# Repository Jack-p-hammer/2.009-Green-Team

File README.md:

Control logic and arduino code for MIT 2025 2.009 Green Team's project.

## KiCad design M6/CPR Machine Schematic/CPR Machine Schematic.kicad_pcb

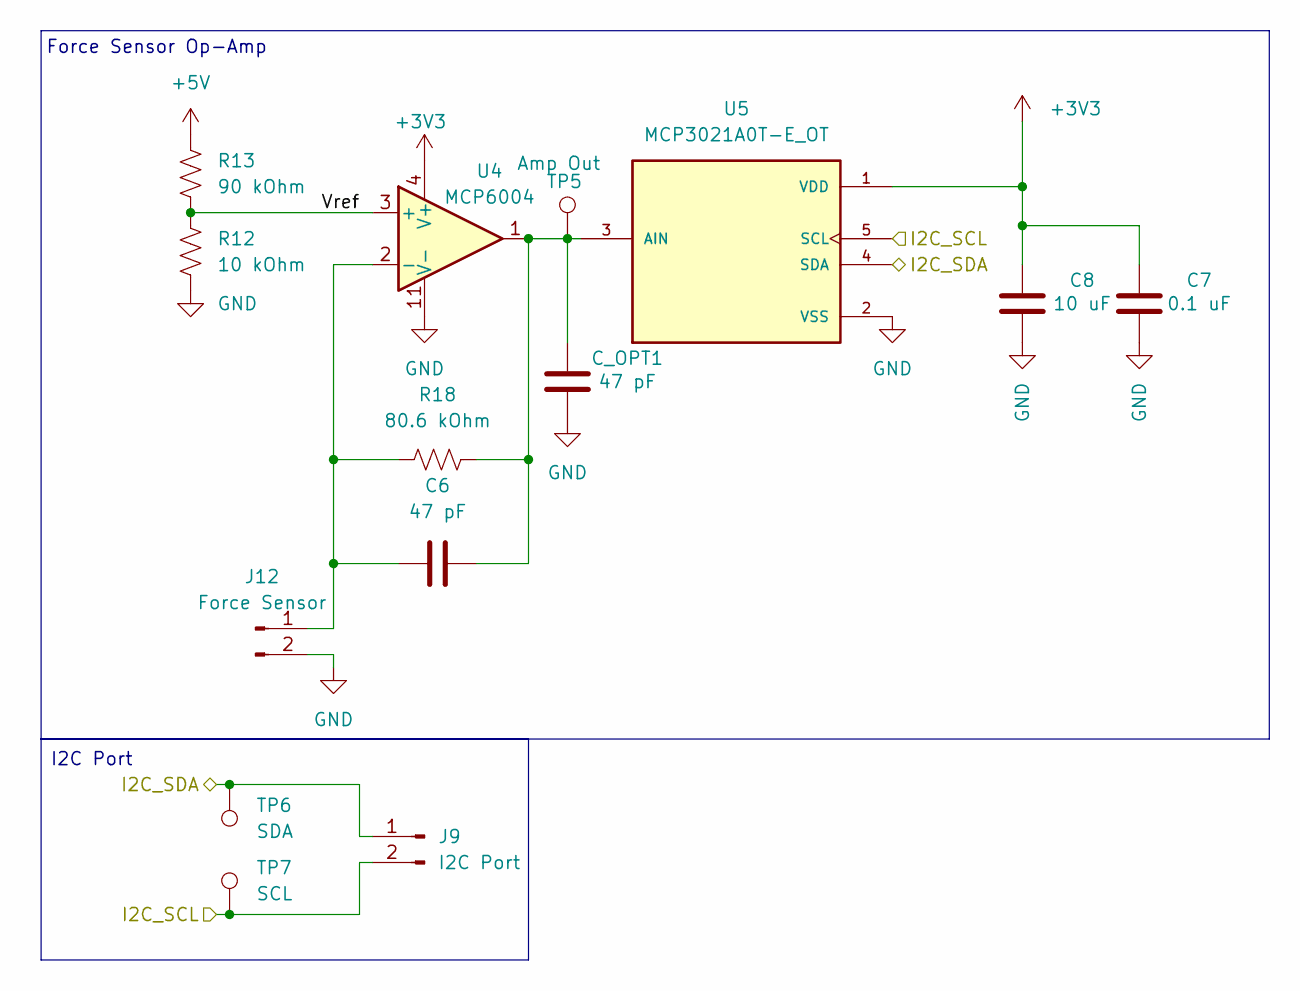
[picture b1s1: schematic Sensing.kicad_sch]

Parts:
C6: 47 pF; C_1206_3216Metric_Pad1.33x1.80mm_HandSolder; digikey 1292-1206N470J102CT-ND
C7: 0.1 uF; C_1206_3216Metric_Pad1.33x1.80mm_HandSolder
C8: 10 uF; C_1206_3216Metric_Pad1.33x1.80mm_HandSolder
C_OPT1: 47 pF; C_1206_3216Metric_Pad1.33x1.80mm_HandSolder
J9: I2C Port; PinHeader_1x02_P2.54mm_Vertical
J12: Force Sensor; TerminalBlock_MaiXu_MX126-5.0-02P_1x02_P5.00mm; digikey 277-1667-ND
R12: 10 kOhm; R_1206_3216Metric_Pad1.30x1.75mm_HandSolder
R13: 90 kOhm; R_1206_3216Metric_Pad1.30x1.75mm_HandSolder; digikey 13-RT1206DRE0790KLCT-ND
R18: 80.6 kOhm; R_1206_3216Metric_Pad1.30x1.75mm_HandSolder; digikey 311-80.6FRCT-ND
TP5: Amp Out; TestPoint_Pad_D1.5mm
TP6: SDA; TestPoint_Pad_D1.5mm
TP7: SCL; TestPoint_Pad_D1.5mm
U4: MCP6004; SOIC14_SL_MCH; digikey MCP6004T-I/SLCT-ND
U5: MCP3021A0T-E_OT; IC_MCP3021A0T-E_OT; PARTREV D; DigiKey_Part_Number MCP3021A0T-E/OTCT-ND

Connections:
+3V3: C7.2, C8.2, U4.4 (V+), U5.1 (VDD)
+5V: R13.1; also elsewhere on the board
/Raspi/I2C_SCL: J9.2, TP7.1, U5.5 (SCL); also elsewhere on the board
/Raspi/I2C_SDA: J9.1, TP6.1, U5.4 (SDA); also elsewhere on the board
/Sensing/Vref: R12.1, R13.2, U4.3 (+)
GND: C7.1, C8.1, C_OPT1.1, J12.2, R12.2, U4.11 (V-), U5.2 (VSS); also elsewhere on the board
unnamed: C6.1, J12.1, R18.2, U4.2 (-)
unnamed: C6.2, C_OPT1.2, R18.1, TP5.1, U4.1, U5.3 (AIN)

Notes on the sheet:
I2C Port
Force Sensor Op-Amp

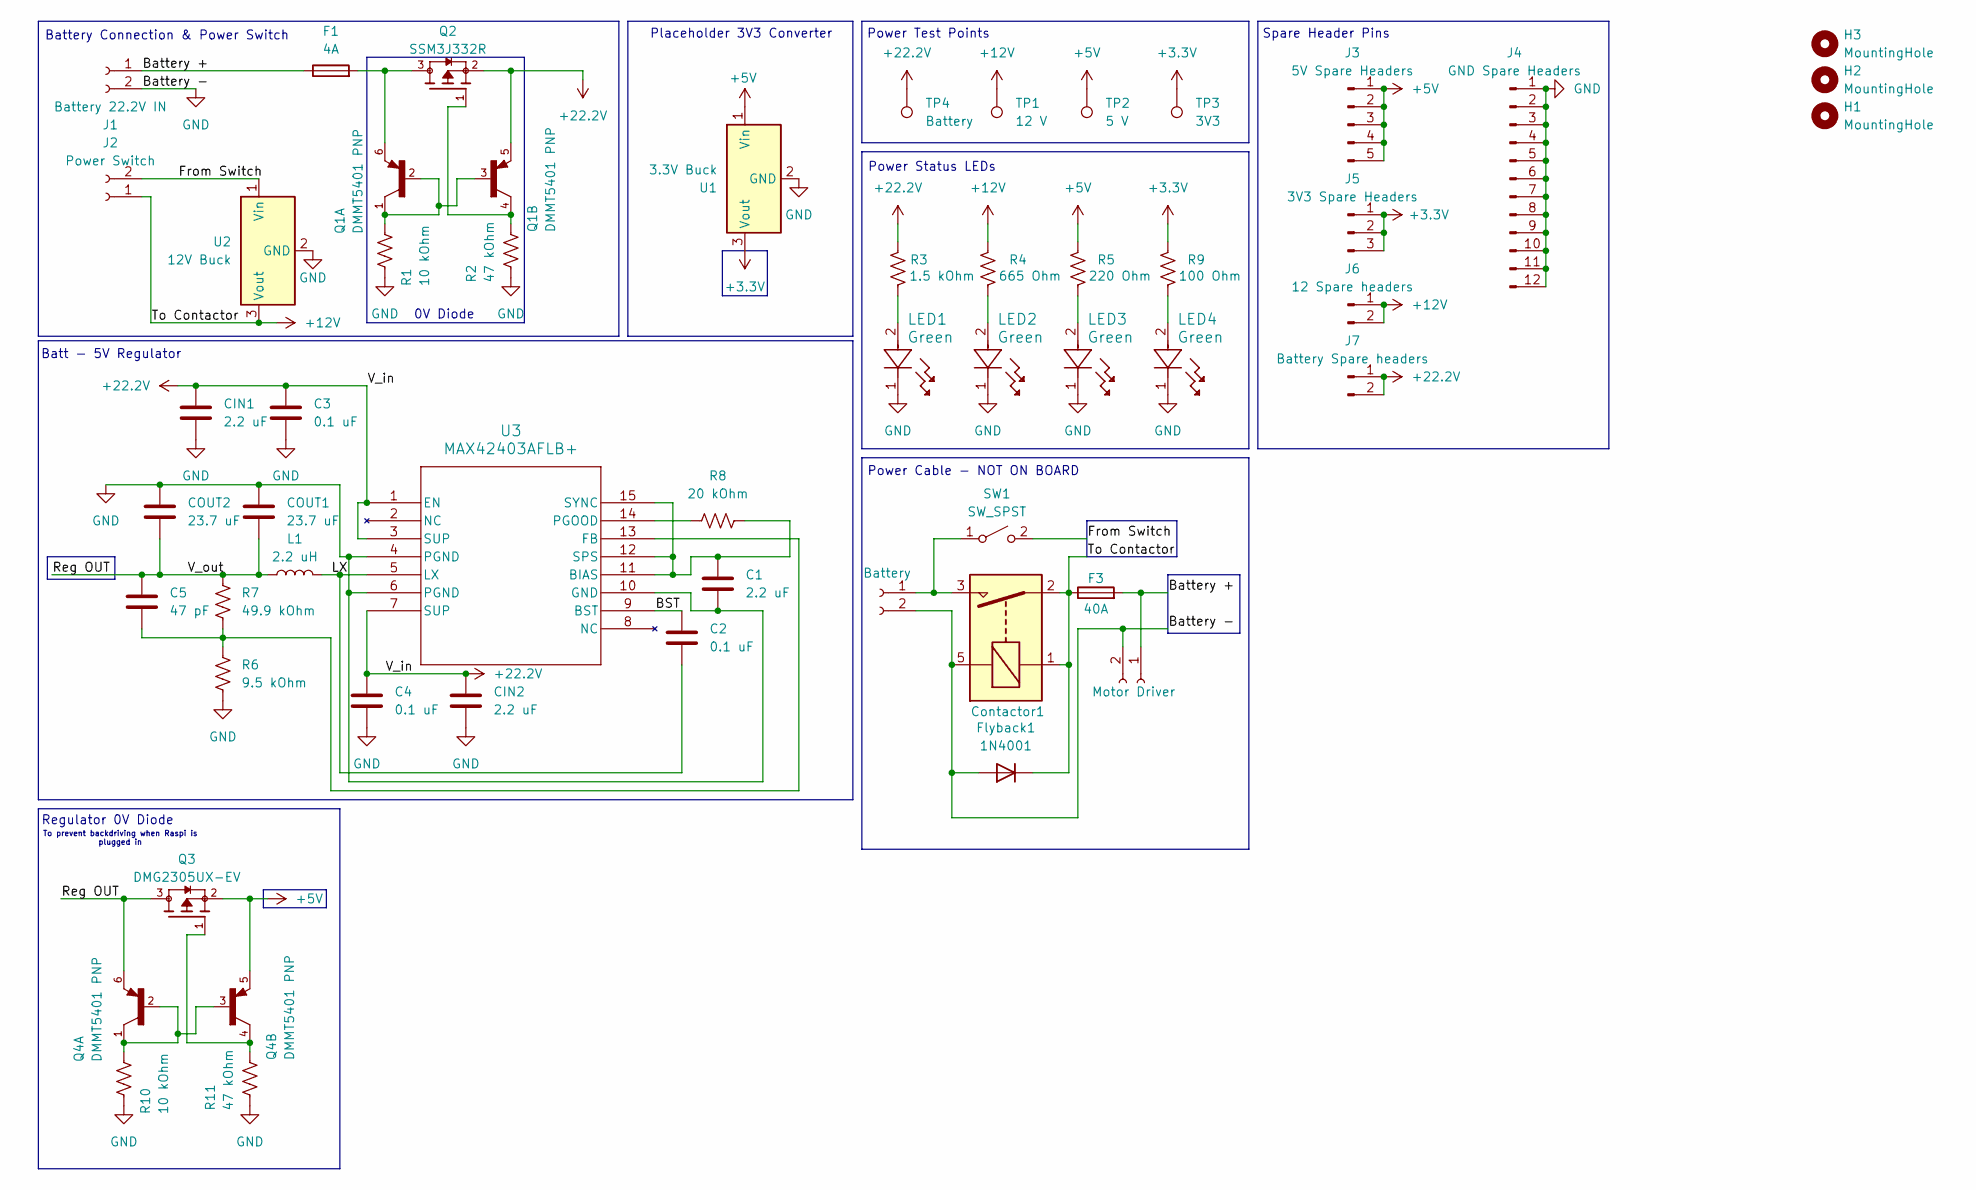
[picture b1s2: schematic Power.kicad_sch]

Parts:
C1: 2.2 uF; C_1206_3216Metric_Pad1.33x1.80mm_HandSolder; digikey 490-17674-1-ND
C2, C3, C4: 0.1 uF; C_1206_3216Metric_Pad1.33x1.80mm_HandSolder; digikey 490-GRM3195C1H104JA05DCT-ND
C5: 47 pF; C_1206_3216Metric_Pad1.33x1.80mm_HandSolder; digikey 1292-1206N470J102CT-ND
CIN1, CIN2: 2.2 uF; C_1206_3216Metric_Pad1.33x1.80mm_HandSolder; digikey 490-17674-1-ND
COUT1, COUT2: 23.7 uF; C_1210_3225Metric_Pad1.33x2.70mm_HandSolder; digikey 490-5312-1-ND
Contactor1: G5Q-1A; Relay_SPST_Omron-G5Q-1A
F1: 4A; Fuse_1206_3216Metric_Pad1.42x1.75mm_HandSolder; digikey 5923-0685T4000-01CT-ND
F3: 40A; Fuse_1206_3216Metric_Pad1.42x1.75mm_HandSolder; digikey 5923-0685T4000-01CT-ND
Flyback1: 1N4001; D_DO-41_SOD81_P10.16mm_Horizontal
H1, H2, H3: MountingHole; MountingHole_2.7mm_M2.5_Pad
J1: Battery 22.2V IN; AMASS_XT30PW-M_1x02_P2.50mm_Horizontal
J2: Power Switch; AMASS_XT30PW-M_1x02_P2.50mm_Horizontal
J3: 5V Spare Headers; PinHeader_1x05_P2.54mm_Vertical
J4: GND Spare Headers; PinHeader_1x12_P2.54mm_Vertical
J5: 3V3 Spare Headers; PinHeader_1x03_P2.54mm_Vertical
J6: 12 Spare headers; PinHeader_1x02_P2.54mm_Vertical
J7: Battery Spare headers; PinHeader_1x02_P2.54mm_Vertical
J16: Motor Driver
J_EXT1: Battery
L1: 2.2 uH; IND_1217AS-H-2R2N=P3; digikey 490-10787-1-ND
LED1, LED2, LED3, LED4: Green; LED_LTST-C170GKT_LTO; digikey 160-1179-1-ND
Q1, Q4: DMMT5401 PNP; SOT95P285X140-6N; PARTREV 8; digikey DMMT5401-FDICT-ND
Q2: SSM3J332R; SOT-23_Handsoldering; digikey SSM3J332RLFCT-ND
Q3: DMG2305UX-EV; SOT-23_Handsoldering; digikey 5272-DMG2305UX-EVCT-ND
R1, R10: 10 kOhm; R_1206_3216Metric_Pad1.30x1.75mm_HandSolder
R2, R11: 47 kOhm; R_1206_3216Metric_Pad1.30x1.75mm_HandSolder; digikey A129830CT-ND
R3: 1.5 kOhm; R_1206_3216Metric_Pad1.30x1.75mm_HandSolder; digikey RMCF1206JG1K50CT-ND
R4: 665 Ohm; R_1206_3216Metric_Pad1.30x1.75mm_HandSolder; digikey 311-665FRCT-ND
R5: 220 Ohm; R_1206_3216Metric_Pad1.30x1.75mm_HandSolder
R6: 9.5 kOhm; R_1206_3216Metric_Pad1.30x1.75mm_HandSolder; digikey 311-9.53KFRCT-ND
R7: 49.9 kOhm; R_1206_3216Metric_Pad1.30x1.75mm_HandSolder; digikey 311-49.9KFRCT-ND
R8: 20 kOhm; R_1206_3216Metric_Pad1.30x1.75mm_HandSolder; digikey RMCF1206FT20K0CT-ND
R9: 100 Ohm; R_1206_3216Metric_Pad1.30x1.75mm_HandSolder
SW1: SW_SPST
TP1: 12 V; TestPoint_THTPad_D4.0mm_Drill2.0mm
TP2: 5 V; TestPoint_THTPad_D4.0mm_Drill2.0mm
TP3: 3V3; TestPoint_THTPad_D4.0mm_Drill2.0mm
TP4: Battery; TestPoint_THTPad_4.0x4.0mm_Drill2.0mm
U1: 3.3V Buck; Converter_DCDC_TRACO_TSR-1_THT; digikey 1951-2742-ND
U2: 12V Buck; Converter_DCDC_TRACO_TSR-1_THT; digikey 1951-2739-ND
U3: MAX42403AFLB+; 21-100701_90-100241_ADI; digikey 505-MAX42403AFLB+-ND

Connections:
+3.3V: J5.1, J5.2, J5.3, R9.2, TP3.1, U1.3 (Vout); also elsewhere on the board
+5V: J3.1, J3.2, J3.3, J3.4, J3.5, Q3.2, Q4.5, R5.2, TP2.1, U1.1 (Vin); also elsewhere on the board
+12V: Contactor1.1, Contactor1.2, F3.1, Flyback1.1 (K), J2.1, J6.1, J6.2, R4.2, TP1.1, U2.3 (Vout)
+22.2V: C3.2, C4.2, CIN1.2, CIN2.2, J7.1, J7.2, Q1.5, Q2.2, R3.2, TP4.1, U3.1 (EN), U3.3 (SUP), U3.7 (SUP)
/Power/BST: C2.2, U3.9 (BST)
/Power/Battery +: F1.1, F3.2, J1.1, J16.1
/Power/From Switch: J2.2, SW1.2 (B), U2.1 (Vin)
/Power/LX: C2.1, L1.2, U3.5 (LX)
/Power/Reg OUT: C5.2, COUT1.1, COUT2.1, L1.1, Q3.3, Q4.6, R7.1
GND: C1.1, C3.1, C4.1, CIN1.1, CIN2.1, COUT1.2, COUT2.2, Contactor1.5, Flyback1.2 (A), J1.2, J4.1, J4.2, J4.3, J4.4, J4.5, J4.6, J4.7, J4.8, J4.9, J4.10, J4.11, J4.12, J16.2, J_EXT1.2, LED1.1, LED2.1, LED3.1, LED4.1, R1.2, R2.2, R6.2, R10.2, R11.2, U1.2 (GND), U2.2 (GND), U3.4 (PGND), U3.6 (PGND), U3.10 (GND); also elsewhere on the board
unnamed: Contactor1.3, J_EXT1.1, SW1.1 (A)
unnamed: F1.2, Q1.6, Q2.3
unnamed: LED1.2, R3.1
unnamed: LED2.2, R4.1
unnamed: LED3.2, R5.1
unnamed: LED4.2, R9.1
unnamed: Q1.4, Q2.1, R2.1
unnamed: Q1.1, Q1.2, Q1.3, R1.1
unnamed: Q4.1, Q4.2, Q4.3, R10.1
unnamed: Q3.1, Q4.4, R11.1
unnamed: C1.2, R8.2, U3.11 (BIAS), U3.12 (SPS), U3.15 (SYNC)
unnamed: C5.1, R6.1, R7.2, U3.13 (FB)
unnamed: R8.1, U3.14 (PGOOD)

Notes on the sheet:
To prevent backdriving when Raspi is plugged in
Battery Connection & Power Switch
Regulator 0V Diode
Batt - 5V Regulator
Power Cable - NOT ON BOARD
Spare Header Pins
Power Status LEDs
Placeholder 3V3 Converter
Power Test Points
0V Diode

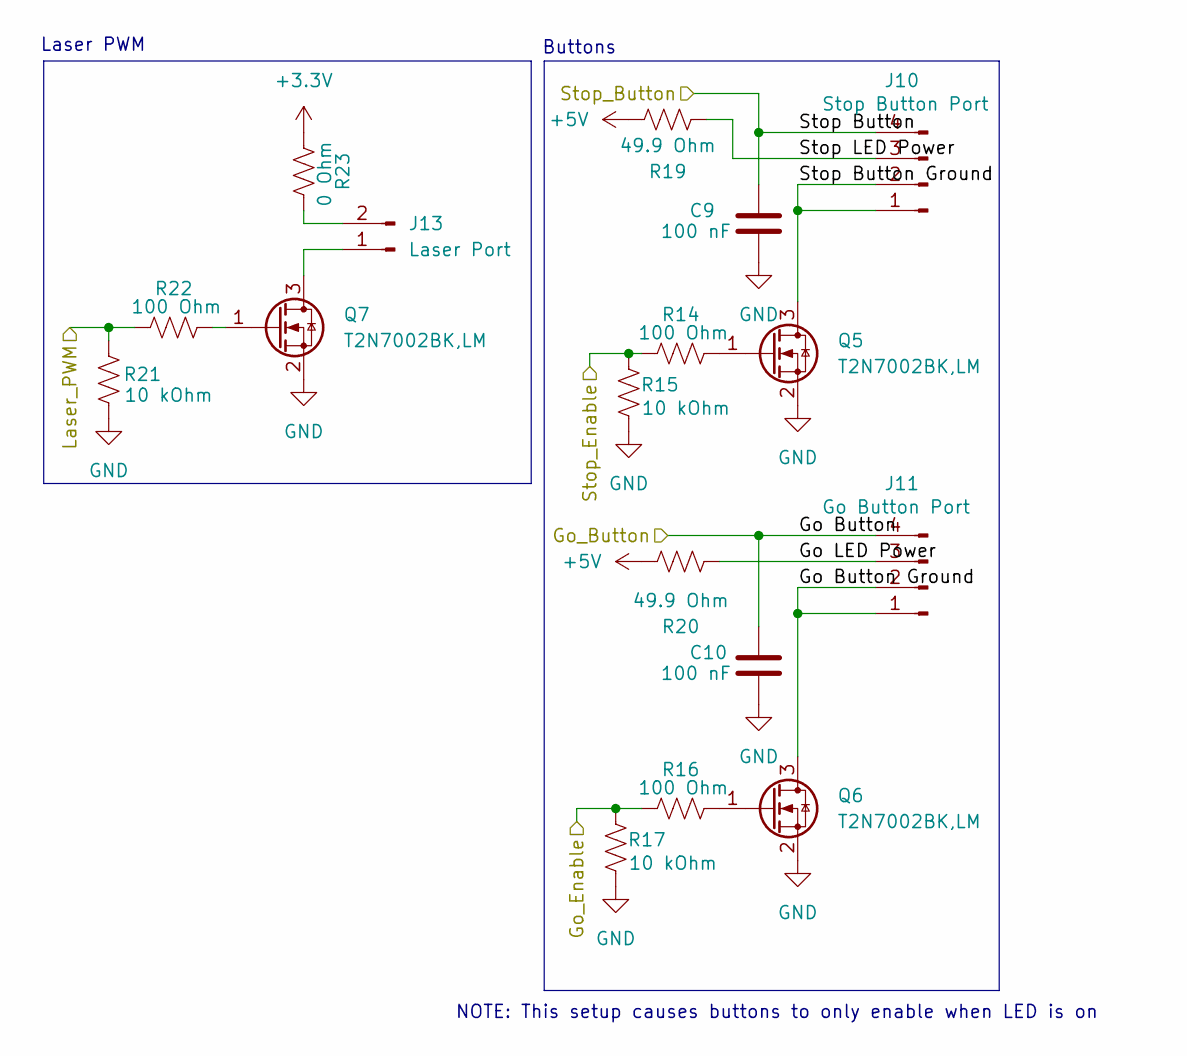
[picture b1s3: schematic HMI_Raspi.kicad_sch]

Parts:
C9, C10: 100 nF; C_1206_3216Metric_Pad1.33x1.80mm_HandSolder
J10: Stop Button Port; PinHeader_1x04_P2.54mm_Vertical
J11: Go Button Port; PinHeader_1x04_P2.54mm_Vertical
J13: Laser Port; TerminalBlock_MaiXu_MX126-5.0-02P_1x02_P5.00mm; digikey 277-1667-ND
Q5, Q6, Q7: T2N7002BK,LM; SOT-23_Handsoldering; digikey T2N7002BKLMCT-ND
R14, R16, R22: 100 Ohm; R_1206_3216Metric_Pad1.30x1.75mm_HandSolder
R15, R17, R21: 10 kOhm; R_1206_3216Metric_Pad1.30x1.75mm_HandSolder
R19, R20: 49.9 Ohm; R_1206_3216Metric_Pad1.30x1.75mm_HandSolder; digikey 311-49.9FRCT-ND
R23: 0 Ohm; R_1206_3216Metric_Pad1.30x1.75mm_HandSolder; digikey RMCF1206ZT0R00CT-ND

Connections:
+3.3V: R23.1; also elsewhere on the board
+5V: R19.2, R20.2; also elsewhere on the board
/HMI_Raspi/Go Button: C10.2, J11.4; also elsewhere on the board
/HMI_Raspi/Go Button Ground: J11.1, J11.2, Q6.3 (D)
/HMI_Raspi/Go LED Power: J11.3, R20.1
/HMI_Raspi/Go_Enable: R16.1, R17.1; also elsewhere on the board
/HMI_Raspi/Laser_PWM: R21.1, R22.1; also elsewhere on the board
/HMI_Raspi/Stop Button: C9.2, J10.4; also elsewhere on the board
/HMI_Raspi/Stop Button Ground: J10.1, J10.2, Q5.3 (D)
/HMI_Raspi/Stop LED Power: J10.3, R19.1
/HMI_Raspi/Stop_Enable: R14.1, R15.1; also elsewhere on the board
GND: C9.1, C10.1, Q5.2 (S), Q6.2 (S), Q7.2 (S), R15.2, R17.2, R21.2; also elsewhere on the board
unnamed: J13.1, Q7.3 (D)
unnamed: J13.2, R23.2
unnamed: Q5.1 (G), R14.2
unnamed: Q7.1 (G), R22.2
unnamed: Q6.1 (G), R16.2

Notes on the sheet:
Buttons
Laser PWM
NOTE: This setup causes buttons to only enable when LED is on

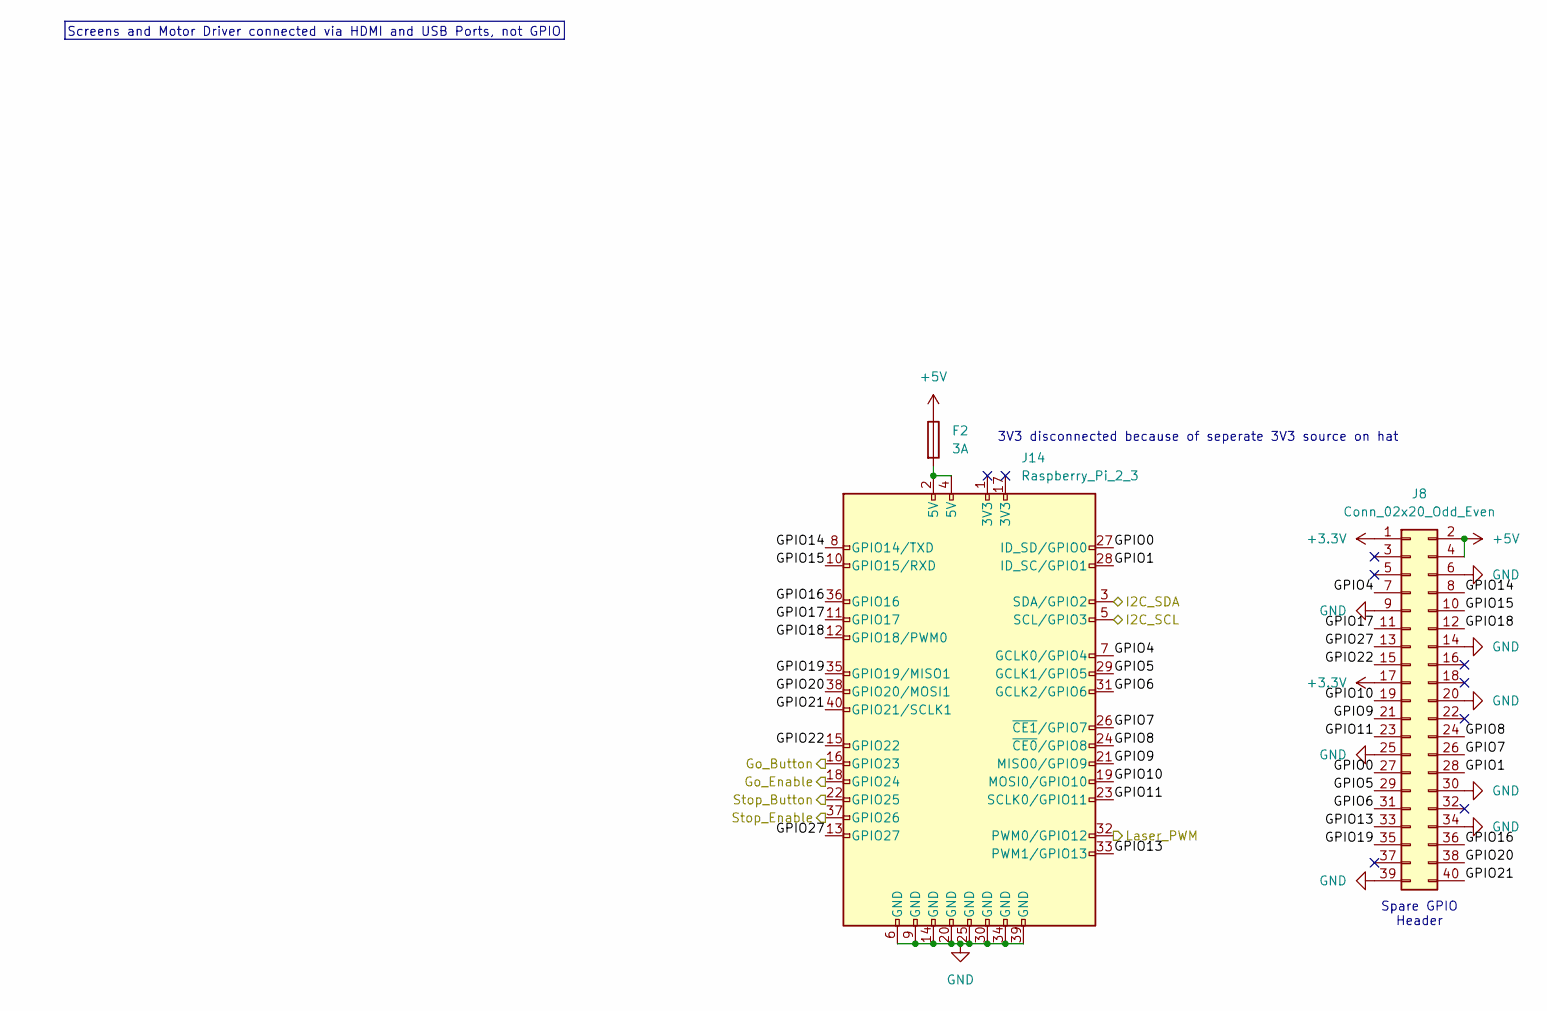
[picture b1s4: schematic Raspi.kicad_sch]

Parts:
F2: 3A; Fuse_1206_3216Metric_Pad1.42x1.75mm_HandSolder; digikey 5923-C1F3CT-ND
J8: Conn_02x20_Odd_Even; PinHeader_2x20_P2.54mm_Vertical
J14: Raspberry_Pi_2_3; PinSocket_2x20_P2.54mm_Vertical

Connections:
+3.3V: J8.1, J8.17; also elsewhere on the board
+5V: F2.1, J8.2, J8.4; also elsewhere on the board
/HMI_Raspi/Go Button: J14.16 (GPIO23); also elsewhere on the board
/HMI_Raspi/Go_Enable: J14.18 (GPIO24); also elsewhere on the board
/HMI_Raspi/Laser_PWM: J14.32 (PWM0/GPIO12); also elsewhere on the board
/HMI_Raspi/Stop Button: J14.22 (GPIO25); also elsewhere on the board
/HMI_Raspi/Stop_Enable: J14.37 (GPIO26); also elsewhere on the board
/Raspi/GPIO0: J8.27, J14.27 (ID_SD/GPIO0)
/Raspi/GPIO1: J8.28, J14.28 (ID_SC/GPIO1)
/Raspi/GPIO4: J8.7, J14.7 (GCLK0/GPIO4)
/Raspi/GPIO5: J8.29, J14.29 (GCLK1/GPIO5)
/Raspi/GPIO6: J8.31, J14.31 (GCLK2/GPIO6)
/Raspi/GPIO7: J8.26, J14.26 (~CE1/GPIO7)
/Raspi/GPIO8: J8.24, J14.24 (~CE0/GPIO8)
/Raspi/GPIO9: J8.21, J14.21 (MISO0/GPIO9)
/Raspi/GPIO10: J8.19, J14.19 (MOSI0/GPIO10)
/Raspi/GPIO11: J8.23, J14.23 (SCLK0/GPIO11)
/Raspi/GPIO13: J8.33, J14.33 (PWM1/GPIO13)
/Raspi/GPIO14: J8.8, J14.8 (GPIO14/TXD)
/Raspi/GPIO15: J8.10, J14.10 (GPIO15/RXD)
/Raspi/GPIO16: J8.36, J14.36 (GPIO16)
/Raspi/GPIO17: J8.11, J14.11 (GPIO17)
/Raspi/GPIO18: J8.12, J14.12 (GPIO18/PWM0)
/Raspi/GPIO19: J8.35, J14.35 (GPIO19/MISO1)
/Raspi/GPIO20: J8.38, J14.38 (GPIO20/MOSI1)
/Raspi/GPIO21: J8.40, J14.40 (GPIO21/SCLK1)
/Raspi/GPIO22: J8.15, J14.15 (GPIO22)
/Raspi/GPIO27: J8.13, J14.13 (GPIO27)
/Raspi/I2C_SCL: J14.5 (SCL/GPIO3); also elsewhere on the board
/Raspi/I2C_SDA: J14.3 (SDA/GPIO2); also elsewhere on the board
GND: J8.6, J8.9, J8.14, J8.20, J8.25, J8.30, J8.34, J8.39, J14.6 (GND), J14.9 (GND), J14.14 (GND), J14.20 (GND), J14.25 (GND), J14.30 (GND), J14.34 (GND), J14.39 (GND); also elsewhere on the board
unnamed: F2.2, J14.2 (5V), J14.4 (5V)

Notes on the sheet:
Spare GPIO Header
Screens and Motor Driver connected via HDMI and USB Ports, not GPIO
3V3 disconnected because of seperate 3V3 source on hat

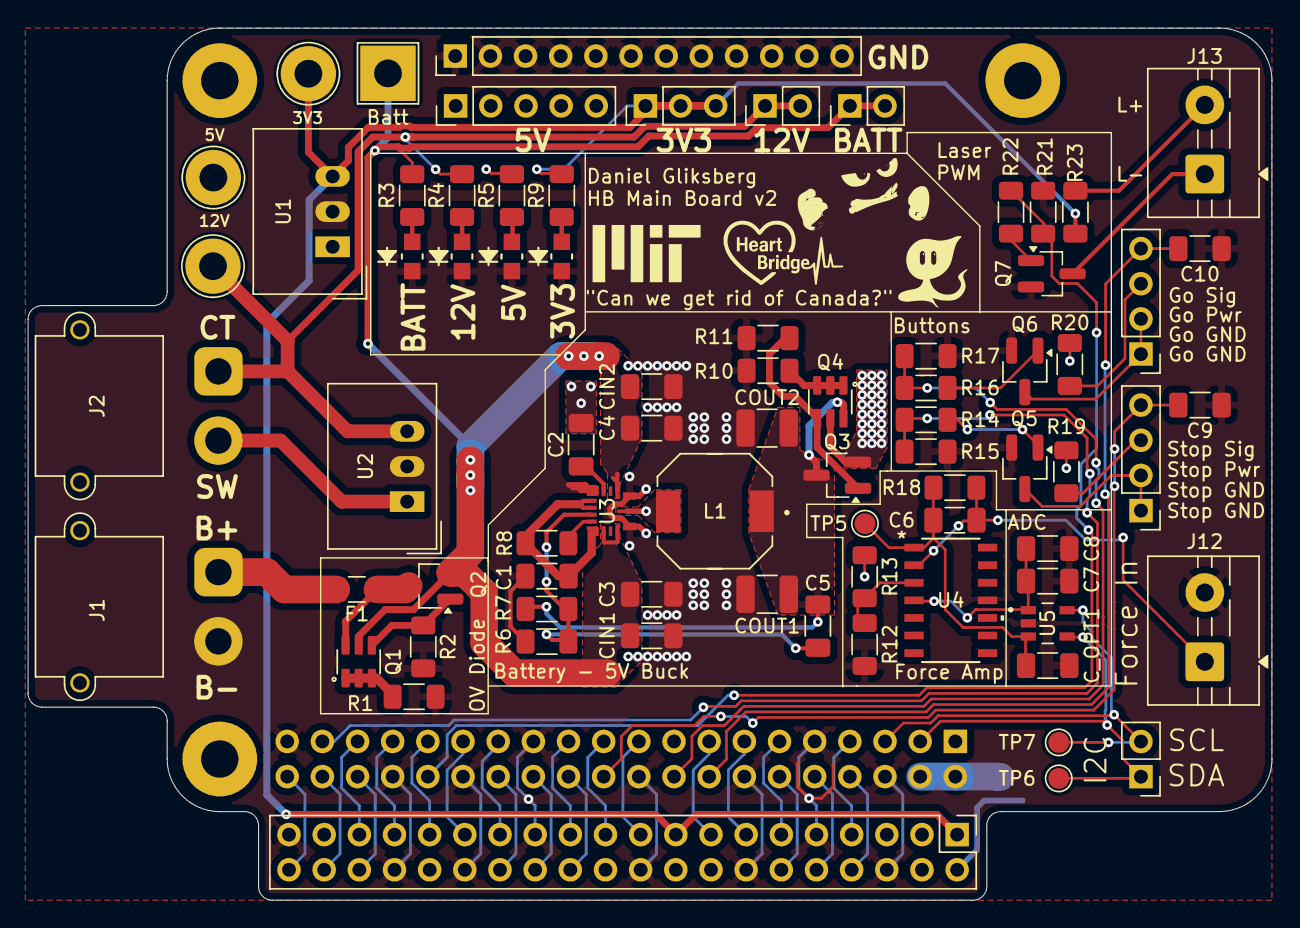
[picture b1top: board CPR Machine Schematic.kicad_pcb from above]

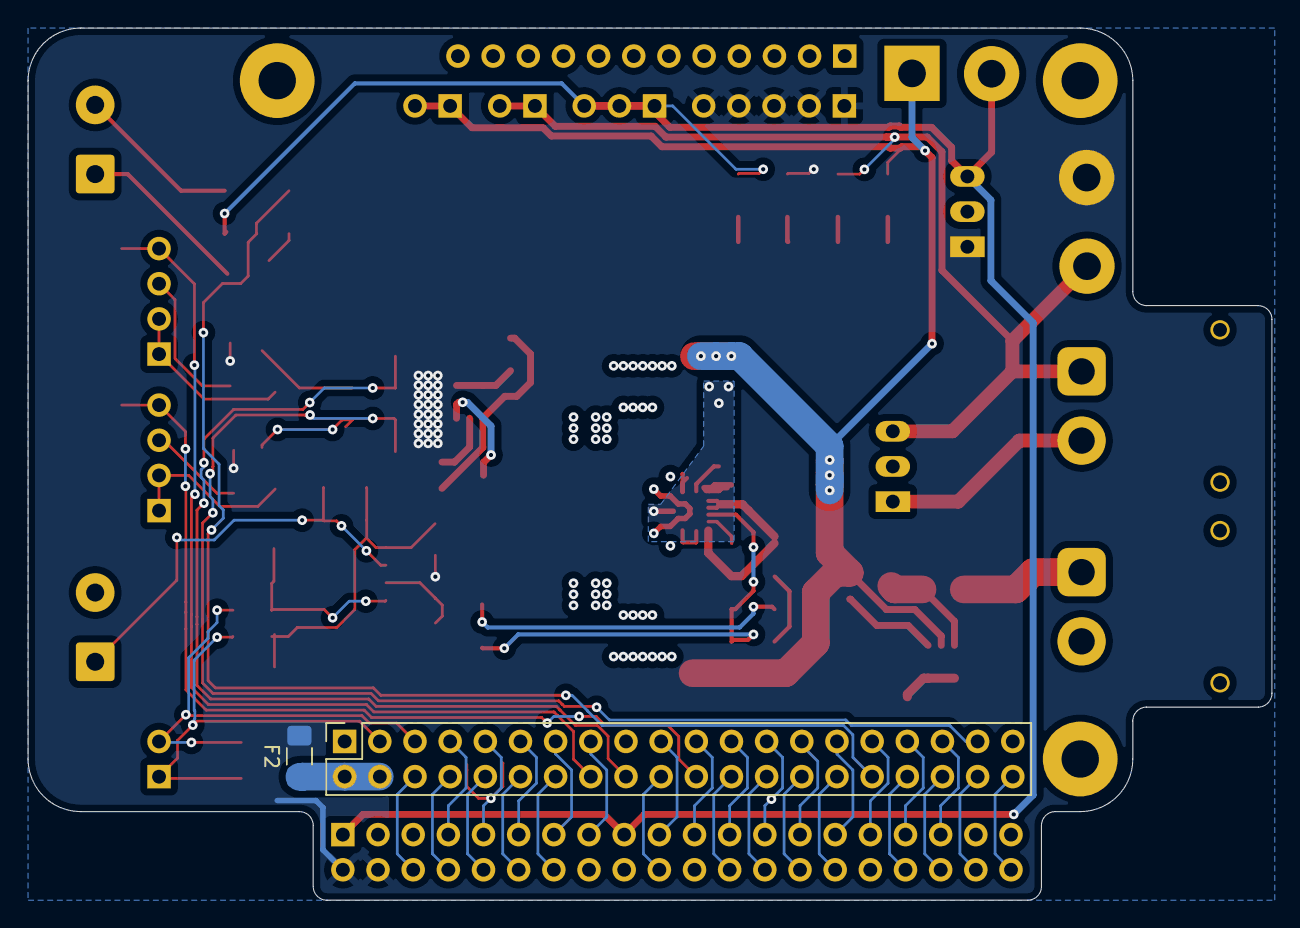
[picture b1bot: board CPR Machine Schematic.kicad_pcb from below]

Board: 2 copper layers, 89.9 x 63.0 mm, 81 parts (2 on the bottom side), 64 nets.

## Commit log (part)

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2025-10-23 adding m3 code
2025-10-23 Arduino Formatting + Basic README
2025-10-23 Added on/off switch, revolutionary technology
2025-10-23 Speed up and fix switch
2025-10-23 motor speed = 0 when off
2025-10-23 actually set speed to 0 when off
2025-10-23 actual off
2025-10-29 ahhhh whats happening
2025-10-30 added platform io folda
2025-10-30 Adding the previous code
2025-10-31 simulink starter added
2025-10-31 sending off for Daniel (my hero)
2025-10-31 Start controller design
    the plant is fucked why is the plant fucked
2025-10-31 Made simulink work kind of, fixed plant TFs
2025-10-31 more TFing
2025-10-31 real numberts, but broken again
2025-10-31 its still fucked oh boy
2025-11-01 PI controller, nyqlog
2025-11-01 Added sensitivity check
2025-11-01 actually save the simlink oobs
2025-11-01 Add rack speed, force, power plotting to simulink
2025-11-01 potential simulink fix
2025-11-01 changing input wave and chest constant
2025-11-01 addition of boilerplate code
2025-11-02 simulink
2025-11-03 more simulated linkage
2025-11-03 Stable force sensing code
2025-11-05 Moteus Motor Driver Integration
2025-11-05 Battery sizing script
2025-11-05 updateee
2025-11-05 P_rms
2025-11-06 plotting n shiii
2025-11-07 Force sensor reading function
2025-11-07 added moteus library submodule
2025-11-07 Figured out moteus library
2025-11-07 killed the scourge that is object-oriented-programming in a case where having functions is less awful
2025-11-07 accurate reference signal
2025-11-07 fiddling w/ crossover
2025-11-07 power calcs
2025-11-08 clean up sim outputs
2025-11-08 remove magic number in min ratio formula
2025-11-08 test higher torque allowance
2025-11-08 Added HMI Environment
2025-11-08 Update moteus subrepo
2025-11-09 Organized motor control code
2025-11-09 Removed boilerplate PIO project
2025-11-09 Organized PIO environments, Prepared for state machine, implemented compression controller calculation
2025-11-09 fixed non-existence of lead in simulink
2025-11-09 nothing changed idk
2025-11-09 Refactor code to minimize repetition
2025-11-09 removed moteus as submodule
2025-11-09 added base for HMI code/env
2025-11-09 Added zeroing capability for encoders
2025-11-09 update zero function comments
2025-11-09 pragma-once-ify sensors.h
2025-11-09 placeholder compression setpoint
2025-11-09 Update controller with slightly lower spring coeff to match EMT experience better
2025-11-09 Updated updateController() to only take one input
2025-11-09 added to state machine enum
2025-11-10 test
2025-11-10 Daniel look at this
2025-11-10 adding ignore, idk why we didnt have this
2025-11-10 new gearbox size
2025-11-11 reaction
2025-11-11 better motor power/current calcs
2025-11-12 read rotary encoder
2025-11-12 think I understand the docs a bit better
2025-11-12 update compress/calib logic to match new updateController() format
2025-11-12 Preliminary/placeholder sensor validation
2025-11-12 Add controller period assert
2025-11-12 update battery sizing logic
2025-11-12 Remove moteus.read() command which doesn't exist
2025-11-12 Added library and code to read ToF sensor
2025-11-12 Cleanup and move state machine variables to control_scheme
2025-11-12 update sensors.cpp to accomidate slow ass ToF sensor
2025-11-12 real MCP2517 pins
2025-11-12 made pinionRadius a global variable
2025-11-12 update dummy position setpoints to not be wrong
2025-11-12 updated SimulinkSetup
2025-11-13 trapezoidal profile update
2025-11-13 trapezoidal motion profile
2025-11-13 More descriptive variable names for computeCompressionSetpoint()
2025-11-13 uodate compression setpoint to be continuous
2025-11-13 update simulink with new setpoint
2025-11-13 slight changes to simulink
2025-11-13 change ToF reading from millis to meters
2025-11-13 make setpoint units explicit in updateController()
2025-11-13 change calib variables from ints to doubles
2025-11-13 make slopes more exact and fix final slope offset
2025-11-13 make force calibrations doubles instead of ints (woops)
2025-11-13 update slimulink with more accurate slopes
2025-11-13 state control ouput units
2025-11-13 make initializeSensors() a bool so we can use it to check if sensor init is succesful
2025-11-13 Change print statements to macros that can be disabled at will
2025-11-13 Rename calibration to zeroing, start state machine
2025-11-13 State machine framework!
2025-11-13 clarify print macro def'n
2025-11-13 dear god
2025-11-13 Helena SPI fix
2025-11-13 Make zero failure an abort case (for now)
2025-11-14 Why aint it workin
2025-11-16 torque motor commands, new matlab setup for no chest, etc
2025-11-16 rename and update compression controller
2025-11-16 Add zeroing controller
2025-11-16 zeroing chill af
2025-11-17 IMU sensor reading code
2025-11-18 ToF calculations
2025-11-18 IMU and TOF file
2025-11-18 Linear enc changes
2025-11-18 SPI pin changes
2025-11-19 Integrating some HMI code into actuator
2025-11-19 sd to display tool
2025-11-19 more integration with HMI
2025-11-19 can test
2025-11-22 KiCAD Start
2025-11-22 More Schematics
2025-11-22 clean up
2025-11-22 Code that works!
2025-11-22 Updated display
2025-11-24 More kiCAD
2025-11-24 morer kicad
2025-11-24 holy fucking shit it works
2025-11-24 HMI Raspi
2025-11-24 HMI schem for real for real
2025-11-24 fixed some forces
2025-11-24 including audio function and pause button
2025-11-24 Setpoint fix, lets get this bread
2025-11-24 Finalized kiCAD
2025-11-24 kicad saves
2025-11-25 Single-pager KiCAD
2025-11-26 zeroing fix - position control weeee
2025-11-27 updated buttons and blinking
2025-11-27 new branch for HMI integration from zeroing
2025-11-27 added file names
2025-11-27 finished integration of showScreen() and playAudio()
2025-11-27 force sensor oobs
2025-11-29 changed force pin on board
2025-12-02 I2S Combination and Screen driver fixes
2025-12-02 Add missing updates to prevState
2025-12-02 display and audio starts automatically when connected to power (no more on button)
2025-12-02 update pins and libs
2025-12-03 added dedicated audio board backup code
2025-12-03 WORKING!!!! button + motor + screen + speaker integration draft 1
2025-12-03 update button pins and spi
2025-12-03 kinda works lol
2025-12-04 old bmp and wav code attempt
2025-12-04 minor changes
2025-12-04 screens on now, still not switching
2025-12-04 YAYYYYYYYYYYYY
2025-12-04 cleaned up battery state
2025-12-04 new retract stuff
2025-12-04 working except retract
2025-12-04 THIS WORKS PERFECT
2025-12-06 HMI changes and force sensor fix
2025-12-06 Move HMI_main out of motor controller src folder
2025-12-06 move HMI_main part 2
2025-12-06 Suppress IMU mentions and unused variable, turn off debug prints
2025-12-06 turn off debug prints
2025-12-06 preliminary anti-pushback code?
2025-12-06 streamlined state machine
2025-12-06 HOLY SHINT IT WORKS OH MY GOD
2025-12-07 position control on zeroing
2025-12-07 fix zeroing (raise setpoint by 0.02 rev)
2025-12-07 double zeroing speed
2025-12-17 Update KiCAD PDF
2026-02-18 Attempt 2 at making main match final
2026-02-20 Start of Schematic V2
2026-03-17 More PCB Progress
    All Footprints
2026-03-20 finished PCB Draft
2026-03-26 PCB Feedback V1
2026-03-28 PCB V2 Part 2
2026-03-29 Down with the second buck converter
2026-03-30 lil guy icon
